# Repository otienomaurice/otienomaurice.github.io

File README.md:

# Engineering Project Portfolio

This is a static portfolio website for hardware and software projects. It is designed for recruiters and resume links: projects can include GitHub repositories, documents, diagrams, source code, build notes, and test reports.

## Edit Your Details

1. Open `index.html`.
2. Replace `YOUR-GITHUB-USERNAME` and `YOUR-LINKEDIN`.
3. Replace `assets/resume.pdf` whenever you want to update the resume shown on the site.
4. Replace the sample project entries in `projects.json` with your real projects.

## Add Documents And Diagrams

Create a `docs` folder and place PDFs, images, CAD exports, diagrams, or reports inside it. Then link them from `projects.json`, for example:

```json
{
  "label": "Architecture diagram",
  "url": "docs/my-project-architecture.pdf"
}
```

## View Locally

Because the site loads `projects.json`, use a local server for the best preview:

```powershell
C:\Users\otien\.cache\codex-runtimes\codex-primary-runtime\dependencies\node\bin\node.exe server.mjs
```

Then open `http://127.0.0.1:8080` on this computer.

To preview from your phone, make sure the phone and computer are on the same Wi-Fi network, then open:

```text
http://YOUR-COMPUTER-IP:8080
```

On Windows, run `ipconfig` and use the IPv4 address for your Wi-Fi adapter.

## Publish

Good simple options:

- GitHub Pages: push this folder to a public repository and enable Pages.
- Netlify: drag this folder into Netlify Drop.
- Vercel: import the repository and deploy as a static site.

The site has no build step and no external runtime dependency.

## Public GitHub Pages Setup

1. Create a public GitHub repository named `maurice-otieno-portfolio` or `YOUR-GITHUB-USERNAME.github.io`.
2. Upload these files to the repository root: `index.html`, `styles.css`, `script.js`, `projects.json`, `.nojekyll`, and the `assets` folder.
3. In the repository, go to `Settings` > `Pages`.
4. Under `Build and deployment`, choose `Deploy from a branch`.
5. Select the `main` branch and `/ (root)`, then save.
6. Wait a few minutes for GitHub to publish the public URL.

## Windows Portfolio Builder App

The portfolio builder is also packaged as a Windows desktop application in `desktop-builder`.

Download the app from the GitHub Releases page:

[OMB Portfolio Builder Windows downloads](https://github.com/otienomaurice/omb-portfolio-builder/releases/latest)

Current release assets include:

- `OMB-Portfolio-Builder-Setup-0.2.1-x64.exe` for a normal Windows installer.
- `OMB-Portfolio-Builder-Portable-0.2.1-x64.exe` for a portable app that runs without installation.

- The app keeps the same builder behavior as the previous local browser workflow.
- Save draft continues to write local draft data.
- Apply to site first verifies GitHub write access, then writes the website catalog, commits changed site files, and pushes to GitHub when the workspace is Git-backed.
- The installer defaults to `C:\Program Files\OMB Portfolio Builder` and lets the user choose a different folder.
- A portable executable is also produced for Windows machines where installation is not desired.

### Install On Another Windows Machine

1. Open the release link above.
2. Download `OMB-Portfolio-Builder-Setup-0.2.1-x64.exe`.
3. Run the installer. The default path is under `C:\Program Files`, but the installer lets you choose another folder.
4. Open **OMB Portfolio Builder** from the Desktop or Start Menu.
5. Install Git for Windows if the machine does not already have Git.
6. Sign in to GitHub through Git Credential Manager using an account that has write access to the website repository.
7. Use **Publishing target** if this machine should publish to a different GitHub Pages repository or custom domain.
8. Optionally enter a GitHub username plus password/token in **Publishing target**. The builder hands this to Git on that Windows machine; it is not committed to the repository.
9. Use **Save draft** first, then **Apply to site** when ready.

### Publishing Security

The builder app is public, but publishing Maurice Otieno's live website is not public.

- The app does not store an owner password and does not embed private credentials.
- `Apply to site` performs a GitHub push permission check before live website files are applied.
- Maurice Otieno's live website can be changed only by a GitHub identity that has write access to `otienomaurice/otienomaurice.github.io`.
- Another user may use the same builder for a different website by opening **Publishing target**, entering their own GitHub Pages/static-site repository URL, optionally entering a custom domain, and authenticating to GitHub with write access to that repository.
- If the signed-in GitHub identity cannot push to the selected target repository, the live website is not changed and the builder stays local-only.
- For custom domains, the builder can write the repository `CNAME` file after the target website repository is associated.
- Use GitHub MFA, Git Credential Manager, and short-lived personal access tokens when stronger approval controls are needed.
- GitHub usually rejects normal account passwords for Git pushes. Use a GitHub personal access token, Git Credential Manager, or an approved organization SSO credential in the password/token field.
- The app works offline for local editing and **Save draft**. When the computer is back online, use **Apply to site** to run the GitHub authorization check and push the saved work.

Build locally:

```powershell
cd desktop-builder
pnpm install
pnpm run dist
```

The GitHub Actions workflow `.github/workflows/build-windows-builder.yml` builds downloadable Windows artifacts. Pushing a tag such as `builder-v0.2.0` creates a GitHub Release with both the installer and portable executable.

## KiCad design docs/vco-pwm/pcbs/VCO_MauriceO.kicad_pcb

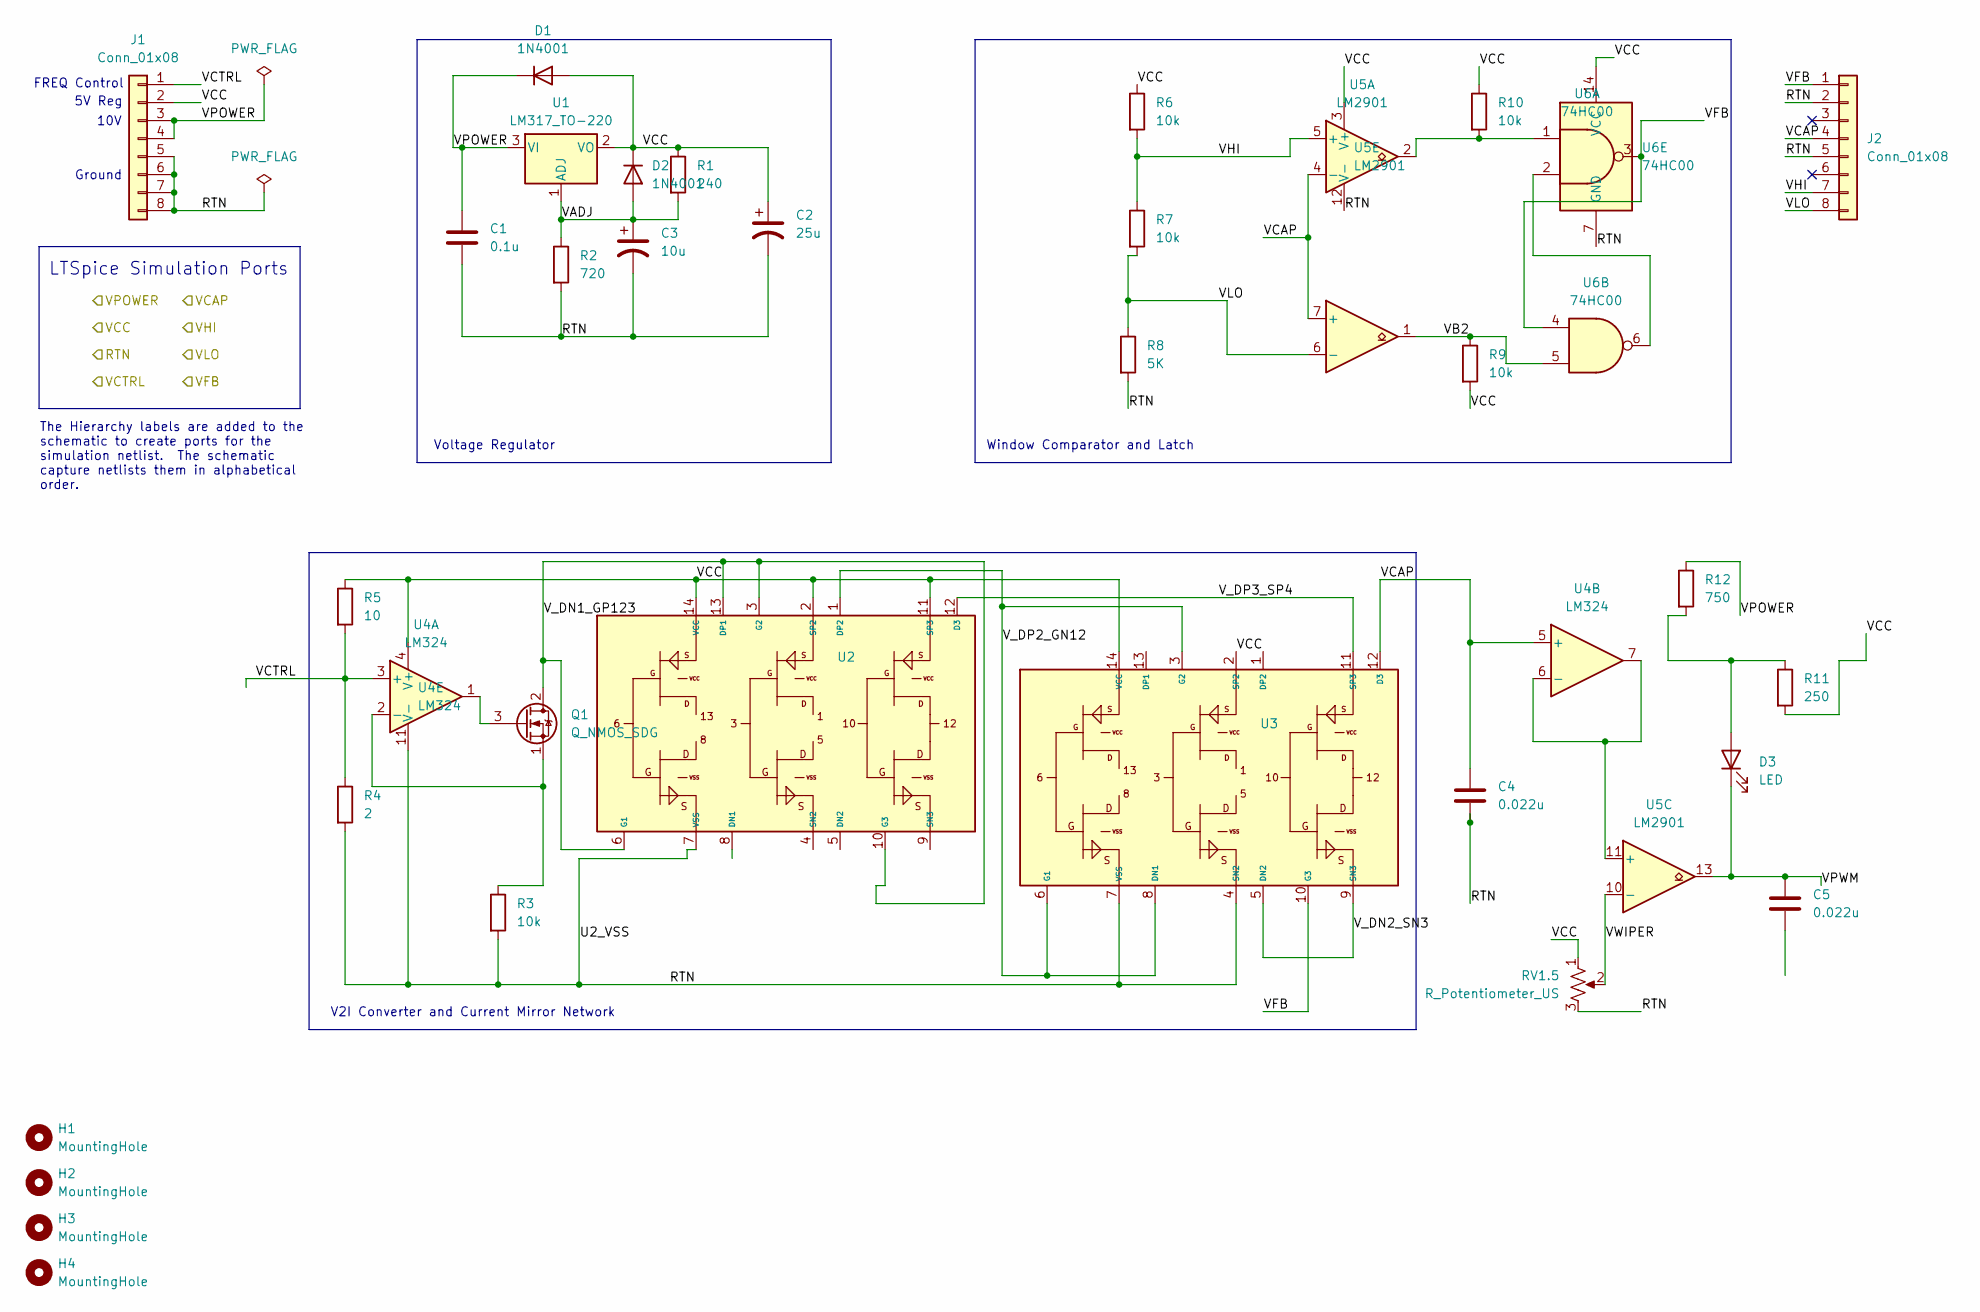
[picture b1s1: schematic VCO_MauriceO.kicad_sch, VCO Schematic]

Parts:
C1: 0.1u; C_Disc_D5.1mm_W3.2mm_P5.00mm
C2: 25u; CP_Radial_D5.0mm_P2.00mm
C3: 10u; CP_Radial_D5.0mm_P2.00mm
C4, C5: 0.022u; C_Disc_D5.1mm_W3.2mm_P5.00mm
D1, D2: 1N4001; D_DO-41_SOD81_P10.16mm_Horizontal
D3: LED; LED_D5.0mm
H1, H2, H3, H4: MountingHole; MountingHole_3.2mm_M3_ISO14580_Pad_TopBottom
J1, J2: Conn_01x08; PinHeader_1x08_P2.54mm_Vertical
Q1: Q_NMOS_SDG; TO-92L_Inline_Wide
R1: 240; R_Axial_DIN0207_L6.3mm_D2.5mm_P15.24mm_Horizontal
R2: 720; R_Axial_DIN0207_L6.3mm_D2.5mm_P15.24mm_Horizontal
R3, R6, R7, R9, R10: 10k; R_Axial_DIN0207_L6.3mm_D2.5mm_P15.24mm_Horizontal
R4: 2; R_Axial_DIN0207_L6.3mm_D2.5mm_P15.24mm_Horizontal
R5: 10; R_Axial_DIN0207_L6.3mm_D2.5mm_P15.24mm_Horizontal
R8: 5K; R_Axial_DIN0207_L6.3mm_D2.5mm_P15.24mm_Horizontal
R11: 250; R_Axial_DIN0207_L6.3mm_D2.5mm_P15.24mm_Horizontal
R12: 750; R_Axial_DIN0207_L6.3mm_D2.5mm_P15.24mm_Horizontal
RV1.5: R_Potentiometer_US; Potentiometer_Alps_RK09Y11_Single_Horizontal
U1: LM317_TO-220; TO-220-3_Vertical
U2, U3: DIP-14_W7.62mm_Socket_LongPads
U4: LM324; DIP-14_W7.62mm_Socket_LongPads
U5: LM2901; DIP-14_W7.62mm_Socket_LongPads
U6: 74HC00; DIP-14_W7.62mm_Socket_LongPads

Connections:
/RTN: C1.2, C2.2, C3.2, C4.2, J1.5, J1.6, J1.7, J1.8, J2.2, J2.5, R2.2, R3.2, R4.2, R8.2, RV1.5.3, U2.7 (VSS), U3.4 (SN2), U3.7 (VSS), U4.11 (V-), U5.12 (V-), U6.7 (GND)
/VADJ: C3.1, D2.2 (A), R1.2, R2.1, U1.1 (ADJ)
/VB2: R9.1, U5.1, U6.5
/VCAP: C4.1, J2.4, U3.12 (D3), U4.5 (+), U5.4 (-), U5.7 (+)
/VCC: C2.1, D1.2 (A), D2.1 (K), J1.2, R1.1, R5.1, R6.1, R9.2, R10.1, R11.2, RV1.5.1, U1.2 (VO), U2.2 (SP2), U2.11 (SP3), U2.14 (VCC), U3.2 (SP2), U3.14 (VCC), U4.4 (V+), U5.3 (V+), U6.14 (VCC)
/VCTRL: J1.1, R4.1, R5.2, U4.3 (+)
/VFB: J2.1, U3.10 (G3), U6.3, U6.4
/VHI: J2.7, R6.2, R7.1, U5.5 (+)
/VLO: J2.8, R7.2, R8.1, U5.6 (-)
/VPOWER: C1.1, D1.1 (K), J1.3, J1.4, R12.1, U1.3 (VI)
/VPWM: C5.1, D3.1 (K), U5.13
/VWIPER: RV1.5.2, U5.10 (-)
/V_DN1_GP123: Q1.2 (D), U2.3 (G2), U2.6 (G1), U2.10 (G3), U2.13 (DP1)
/V_DN2_SN3: U3.5 (DN2), U3.9 (SN3)
/V_DP2_GN12: U2.1 (DP2), U3.3 (G2), U3.6 (G1), U3.8 (DN1)
/V_DP3_SP4: U2.12 (D3), U3.11 (SP3)
unnamed: D3.2 (A), R11.1, R12.2
unnamed: Q1.3 (G), U4.1
unnamed: Q1.1 (S), R3.1, U4.2 (-)
unnamed: R10.2, U5.2, U6.1
unnamed: U4.6 (-), U4.7, U5.11 (+)
unnamed: U6.2, U6.6

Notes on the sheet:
5V Reg
V2I Converter and Current Mirror Network
Ground
LTSpice Simulation Ports
10V
Window Comparator and Latch
FREQ Control
Voltage Regulator
The Hierarchy labels are added to the schematic to create ports for the simulation netlist. The schematic capture netlists them in alphabetical order.

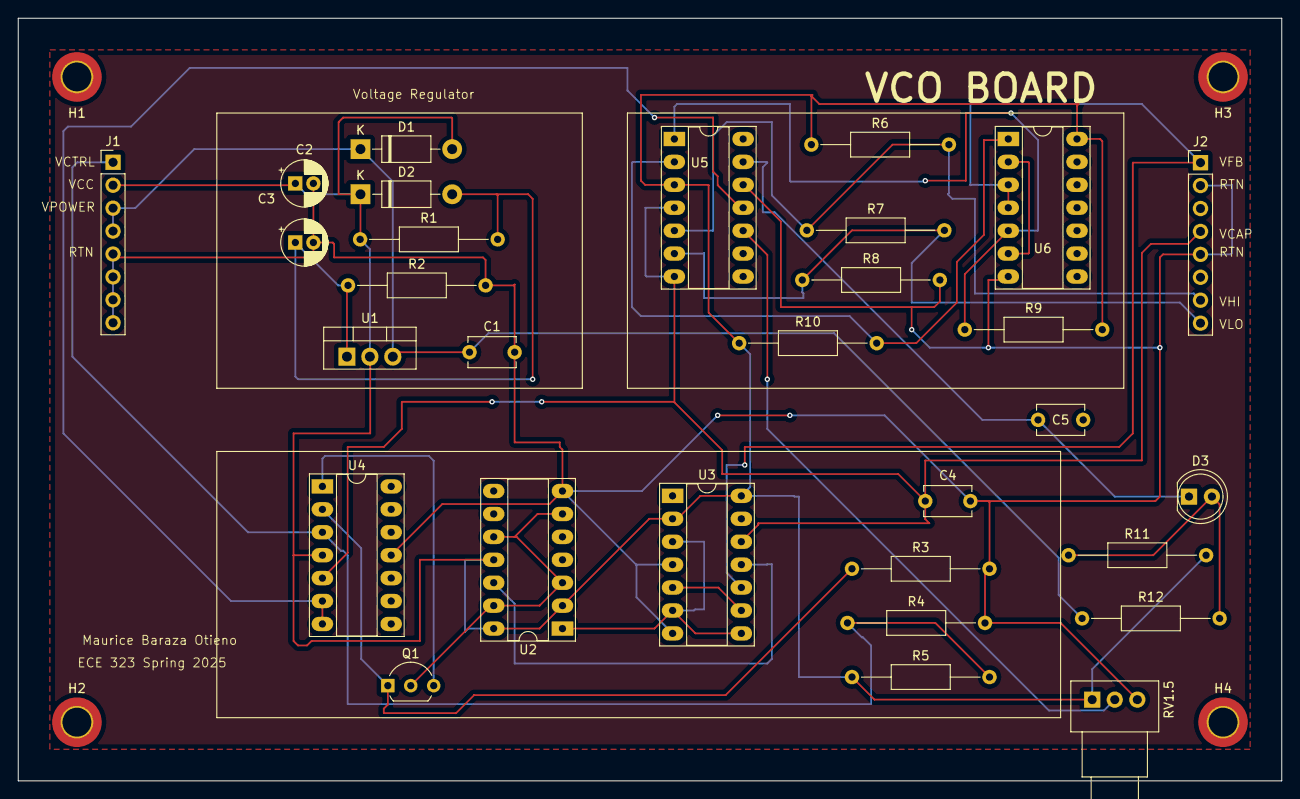
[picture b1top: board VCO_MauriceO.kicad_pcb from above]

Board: 2 copper layers, 140.0 x 84.5 mm, 34 parts (0 on the bottom side), 22 nets.

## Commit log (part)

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2026-06-03 Create portfolio website
2026-06-03 Use Maurice GitHub profile links
2026-06-03 Use correct GitHub account links
2026-06-04 Configure custom domain
2026-06-04 Add profile photo to contact section
2026-06-04 Move GitHub links to otienomaurice account
2026-06-04 Add OMB header mark and avatar
2026-06-04 Improve search engine discoverability
2026-06-04 Refresh hero with light blue lab background
2026-06-04 Replace hero with analog circuit background
2026-06-04 Use natural dark analog hero
2026-06-04 Revert "Use natural dark analog hero"
    This reverts commit 2b6c586fa3acef57216f586596fc2298c1e2f905.
2026-06-04 Refine public portfolio copy
2026-06-04 Add hardware project catalog architecture
2026-06-04 Add PWM VCO portfolio project
2026-06-06 Update portfolio site 2026-06-06
2026-06-06 Refactor templates into shared visual skins
2026-06-07 Update portfolio site 2026-06-07
2026-06-08 Update portfolio site 2026-06-08
2026-06-09 Update portfolio site 2026-06-09
2026-06-10 Update portfolio site 2026-06-10
2026-06-11 Update portfolio site 2026-06-11
2026-06-12 Update portfolio site 2026-06-12
2026-06-18 Update portfolio site 2026-06-18
2026-06-18 Trigger Pages rebuild for browser navigation
2026-06-18 Improve portfolio search experience
2026-06-19 Update portfolio site 2026-06-19
2026-06-19 Add portfolio AI assistant
2026-06-19 Refine portfolio AI assistant
2026-06-19 Add portfolio AI backend endpoint
2026-06-19 Refine portfolio AI chat behavior
2026-06-19 Stabilize contact AI layout and intelligence
2026-06-20 Update portfolio site 2026-06-20
2026-06-20 Add Workers AI backend fallback
2026-06-20 Improve portfolio AI routing and chat readability
2026-06-20 Fix mobile contact AI order
2026-06-20 Improve project section navigation and overview display
2026-06-20 update AI intelligence
2026-06-20 Improve portfolio AI sources and window controls
2026-06-20 Expand portfolio AI intelligence
2026-06-20 Allow longer portfolio AI source requests
2026-06-20 Refresh portfolio AI client script
2026-06-20 Prioritize GitHub code for portfolio AI
2026-06-20 Prevent hypothetical repository code
2026-06-21 Improve portfolio AI conversation flow
2026-06-21 Use deployed AI endpoint for local preview
2026-06-21 Refresh AI conversation script cache
2026-06-21 Make AI portfolio links prompt-specific
2026-06-21 Add OMB favicon and desktop builder app
2026-06-21 Migrate portfolio builder to Windows desktop app
2026-06-21 Clarify portfolio AI public GitHub access
2026-06-21 Update portfolio site 2026-06-21
2026-06-21 Add secure publishing target configuration
2026-06-21 Disable desktop builder implicit publish
2026-06-22 Add portfolio profile metadata
2026-06-22 Update portfolio site 2026-06-22
2026-06-22 Add builder application download link
2026-06-23 Update portfolio site 2026-06-23
2026-06-27 Update portfolio site 2026-06-27
2026-06-28 Point builder download to latest installer
